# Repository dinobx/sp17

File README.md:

# SP17

**SP17** is a silly little macropad inspired on the optimal solution for packing 17 equal squares into the smallest possible bounding square.

Based on the mathematical packing problem: how can you fit a certain amount of unit squares into the smallest possible rectangle? Read more about the packing problem of x squares on https://www.combinatorics.org/files/Surveys/ds7/ds7v5-2009/ds7-2009.html

## Details

- 17 keys in the optimal packing solution for 17 squares, with options to opt for 2u vertical or horizontal keys in the bottom corners
- MX-compatible, solder only
- Diodeless
- Pro Micro footprint
- Silicone bumper feet cutout on the bottom
- 0° typing angle
- Features the 40%s community Logo where this project originated from
- The PCB has been prototyped by JLCPCB and confirmed to work using the "SP17 PCB.zip" in [production](SP17%20PCB/production)
- The Case was designed and optimized for CNC milling, but is also 3D printable. A CNC'd case has not been prototyped before
- If interest persist a small Groupbuy may be held eventually

## License and Disclaimer

This project is released under the [MIT License](LICENSE). You're free to use, remix, fork, or manufacture this however you want. I am not responsible for any mishaps if you order the PCB or case as-is, however I am confident that there are no issues with this simple design.

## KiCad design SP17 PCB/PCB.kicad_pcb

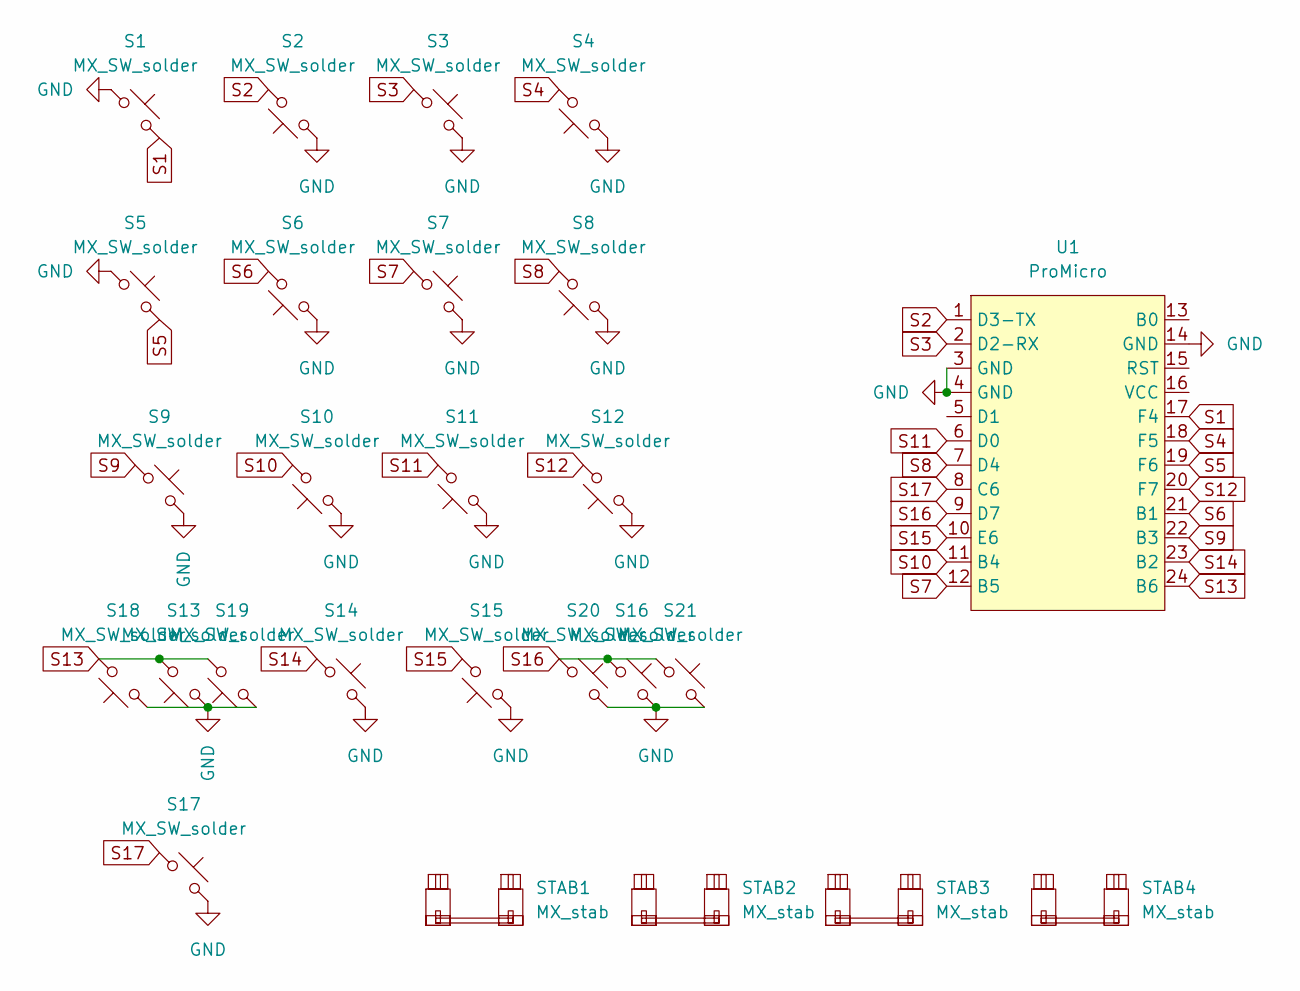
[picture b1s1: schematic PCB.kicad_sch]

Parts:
S1, S2, S3, S4, S5, S6, S7, S8, S9, S10, S11, S12, S13, S14, S15, S16, S17, S18, S19, S20, S21: MX_SW_solder; SW_MX_1u
STAB1, STAB2, STAB3, STAB4: MX_stab; STAB_MX_2u
U1: ProMicro; ProMicro_USBup

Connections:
GND: S1.1, S2.1, S3.2, S4.1, S5.1, S6.1, S7.2, S8.1, S9.2, S10.1, S11.1, S12.1, S13.1, S14.2, S15.1, S16.2, S17.2, S18.1, S19.1, S20.2, S21.2, U1.3 (GND), U1.4 (GND), U1.14 (GND)
S1: S1.2, U1.17 (F4)
S2: S2.2, U1.1 (D3-TX)
S3: S3.1, U1.2 (D2-RX)
S4: S4.2, U1.18 (F5)
S5: S5.2, U1.19 (F6)
S6: S6.2, U1.21 (B1)
S7: S7.1, U1.12 (B5)
S8: S8.2, U1.7 (D4)
S9: S9.1, U1.22 (B3)
S10: S10.2, U1.11 (B4)
S11: S11.2, U1.6 (D0)
S12: S12.2, U1.20 (F7)
S13: S13.2, S18.2, S19.2, U1.24 (B6)
S14: S14.1, U1.23 (B2)
S15: S15.2, U1.10 (E6)
S16: S16.1, S20.1, S21.1, U1.9 (D7)
S17: S17.1, U1.8 (C6)

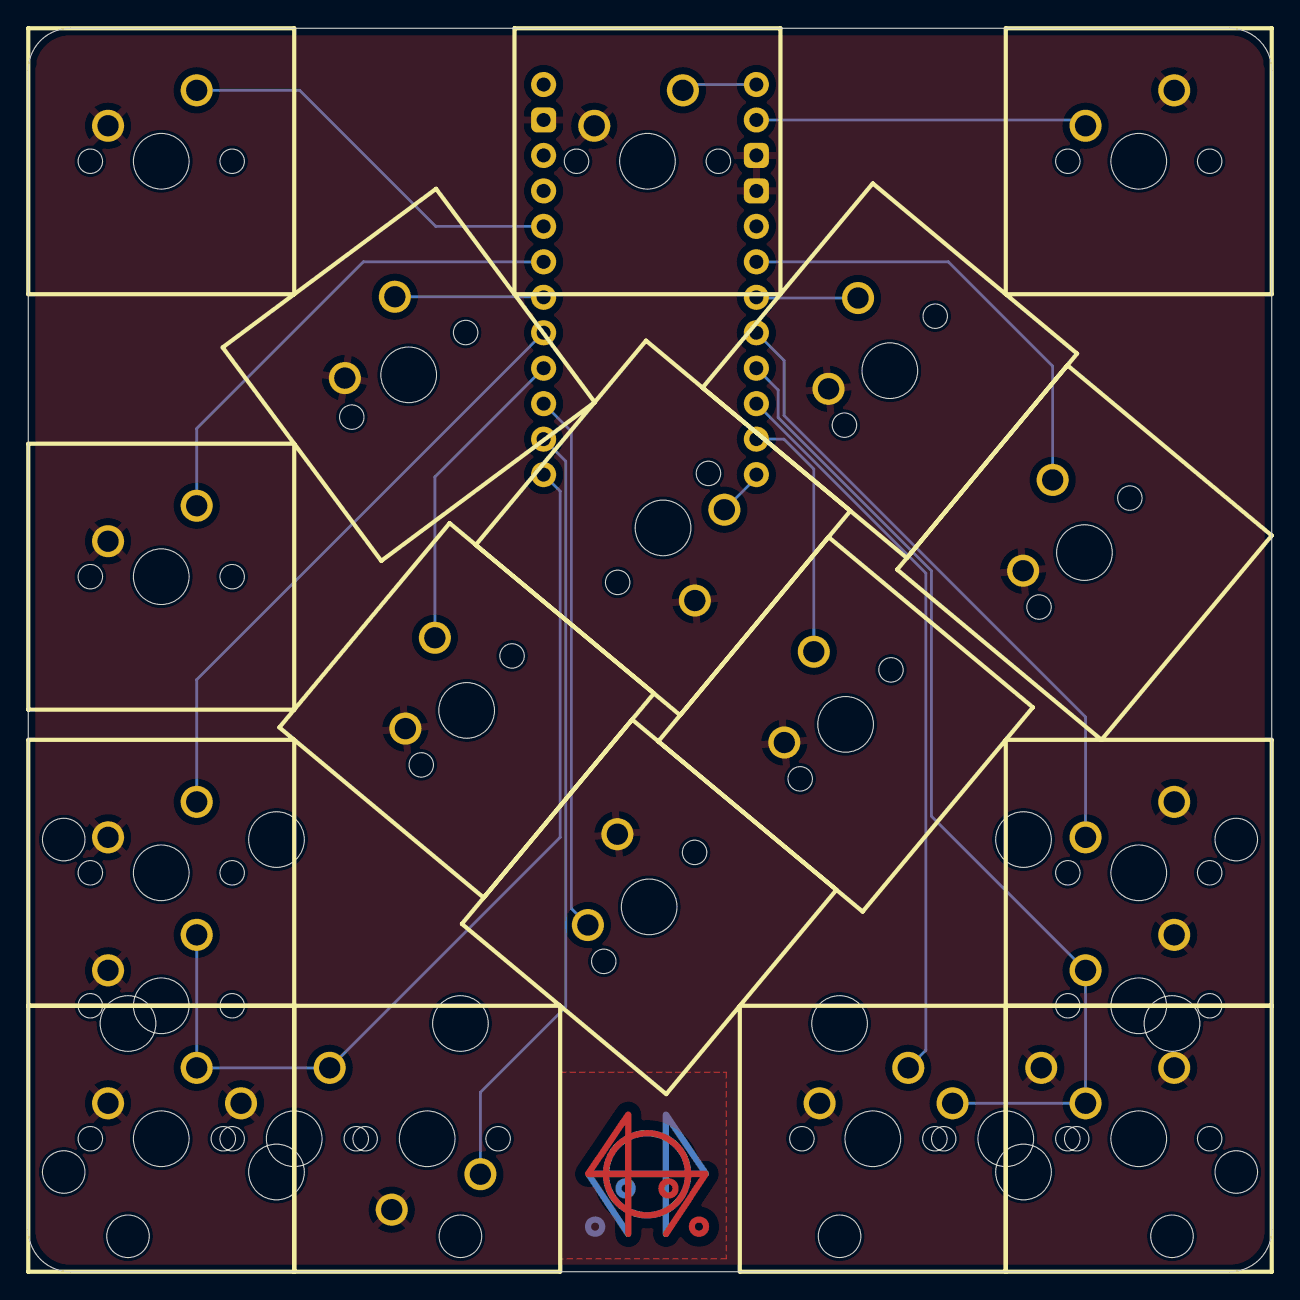
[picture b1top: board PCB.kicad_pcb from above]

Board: 2 copper layers, 89.1 x 89.1 mm, 26 parts (1 on the bottom side), 18 nets.

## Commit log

2025-06-27 added SP17 MonoCase.step file
2025-06-27 added KiCad PCB
2025-06-27 added production/PCB.zip
2025-06-27 Create LICENSE
2025-06-27 replaced case file, added stl
2025-06-27 added (outdated) vial.uf2 vial firmware
